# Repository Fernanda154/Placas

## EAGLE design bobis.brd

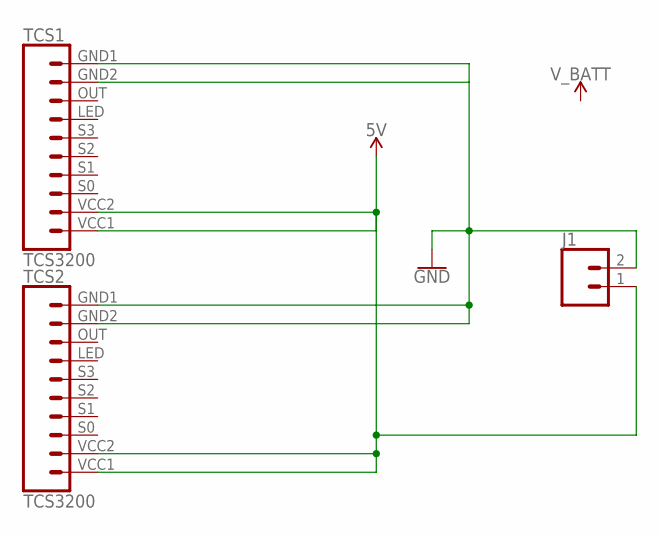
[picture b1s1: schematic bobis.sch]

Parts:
J1: CONN_02; 1X02
TCS1, TCS2: TCS3200

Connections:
5V: J1.1, TCS1.VCC1, TCS1.VCC2, TCS2.VCC1, TCS2.VCC2
GND: J1.2, TCS1.GND1, TCS1.GND2, TCS2.GND1, TCS2.GND2

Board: 2 copper layers, 3 parts (0 on the bottom side), 2 nets, no tracks yet.

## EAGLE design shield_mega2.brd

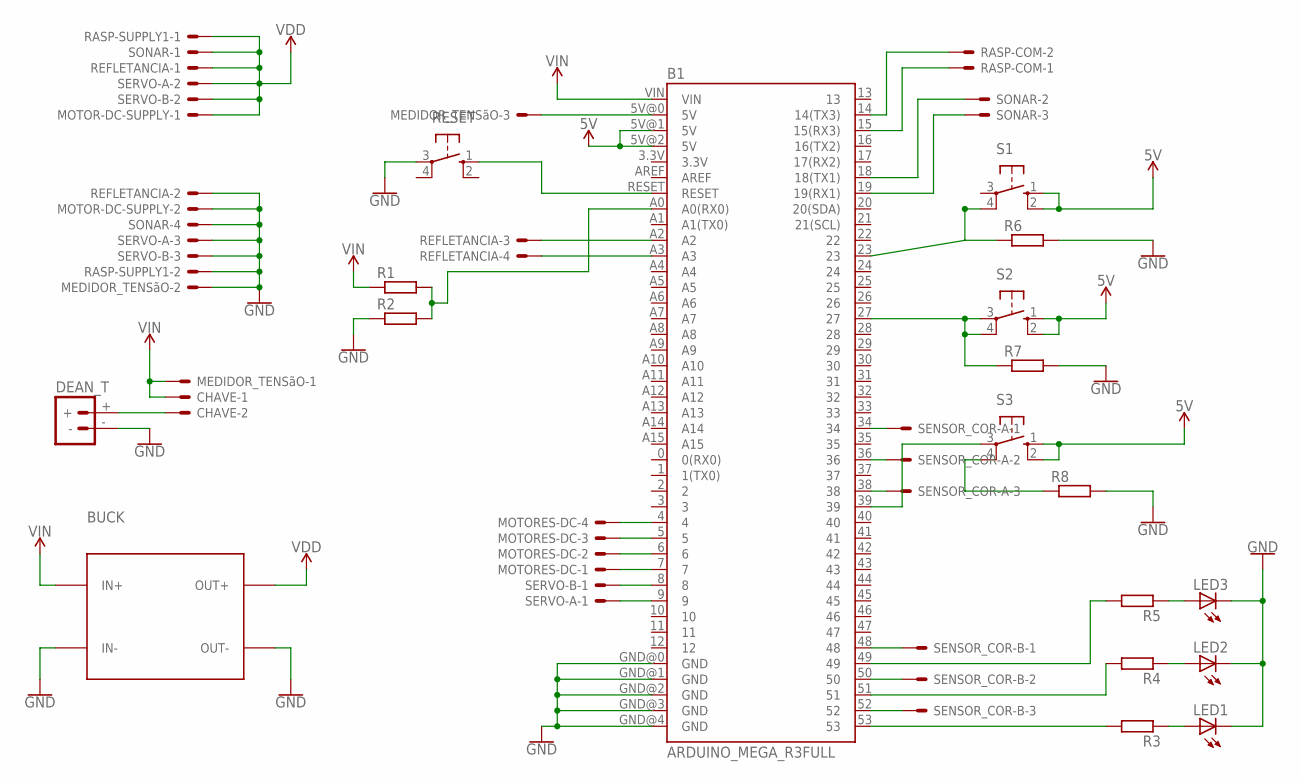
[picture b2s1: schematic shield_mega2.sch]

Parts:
B1: ARDUINO_MEGA_R3FULL; ARDUINO_MEGA
BUCK: DC-DC-STEP-DOWN-LM2596
CHAVE: 22-23-2021
DEAN_T: BATTERY_CONN_DEANS; DEANS
LED1, LED2, LED3: LED5MM
MEDIDOR_TENSãO: 22-23-2031
MOTOR-DC-SUPPLY: 22-23-2021
MOTORES-DC: 22-23-2041
R1, R2: R-EU_0207/12; 0207/12
R3, R4, R5: R-EU_0207/7; 0207/7
R6, R7, R8: R-EU_0204/7; 0204/7
RASP-COM: 22-23-2021
RASP-SUPPLY1: 22-23-2021
REFLETANCIA: 22-23-2041
RESET: 10-XX; B3F-10XX
S1, S2, S3: 10-XX; B3F-10XX
SENSOR_COR-A: 22-23-2031
SENSOR_COR-B: 22-23-2031
SERVO-A: 22-23-2031
SERVO-B: 22-23-2031
SONAR: 22-23-2041

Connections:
5V: B1.5V@1 (5V), B1.5V@2 (5V), S1.1 (S), S1.2 (S1), S2.1 (S), S2.2 (S1), S3.1 (S), S3.2 (S1)
GND: B1.GND@0 (GND), B1.GND@1 (GND), B1.GND@2 (GND), B1.GND@3 (GND), B1.GND@4 (GND), BUCK.IN-, BUCK.OUT-, DEAN_T.-, LED1.K (C), LED2.K (C), LED3.K (C), MEDIDOR_TENSãO.2, MOTOR-DC-SUPPLY.2, R2.1, R6.2, R7.2, R8.2, RASP-SUPPLY1.2, REFLETANCIA.2, RESET.3, SERVO-A.3, SERVO-B.3, SONAR.4
unnamed: B1.A2, REFLETANCIA.3
unnamed: B1.A3, REFLETANCIA.4
unnamed: B1.4, MOTORES-DC.4
unnamed: B1.5, MOTORES-DC.3
unnamed: B1.6, MOTORES-DC.2
unnamed: B1.7, MOTORES-DC.1
unnamed: B1.8, SERVO-B.1
unnamed: B1.9, SERVO-A.1
unnamed: B1.14 (14(TX3)), RASP-COM.2
unnamed: B1.15 (15(RX3)), RASP-COM.1
unnamed: B1.18 (18(TX1)), SONAR.2
unnamed: B1.19 (19(RX1)), SONAR.3
unnamed: CHAVE.2, DEAN_T.+
unnamed: B1.34, SENSOR_COR-A.1
unnamed: B1.36, SENSOR_COR-A.2
unnamed: B1.38, SENSOR_COR-A.3
unnamed: B1.52, SENSOR_COR-B.3
unnamed: B1.50, SENSOR_COR-B.2
unnamed: B1.48, SENSOR_COR-B.1
unnamed: B1.A0 (A0(RX0)), R1.2, R2.2
unnamed: B1.53, R3.2
unnamed: B1.51, R4.2
unnamed: B1.49, R5.2
unnamed: LED3.A, R5.1
unnamed: LED2.A, R4.1
unnamed: LED1.A, R3.1
unnamed: B1.27, R7.1, S2.3, S2.4 (P1)
unnamed: B1.23, R6.1, S1.4 (P1)
unnamed: R8.1, S3.4 (P1)
unnamed: B1.39, S3.3
unnamed: B1.RESET, RESET.1 (S)
unnamed: B1.5V@0 (5V), MEDIDOR_TENSãO.3
VDD: BUCK.OUT+, MOTOR-DC-SUPPLY.1, RASP-SUPPLY1.1, REFLETANCIA.1, SERVO-A.2, SERVO-B.2, SONAR.1
VIN: B1.VIN, BUCK.IN+, CHAVE.1, MEDIDOR_TENSãO.1, R1.1

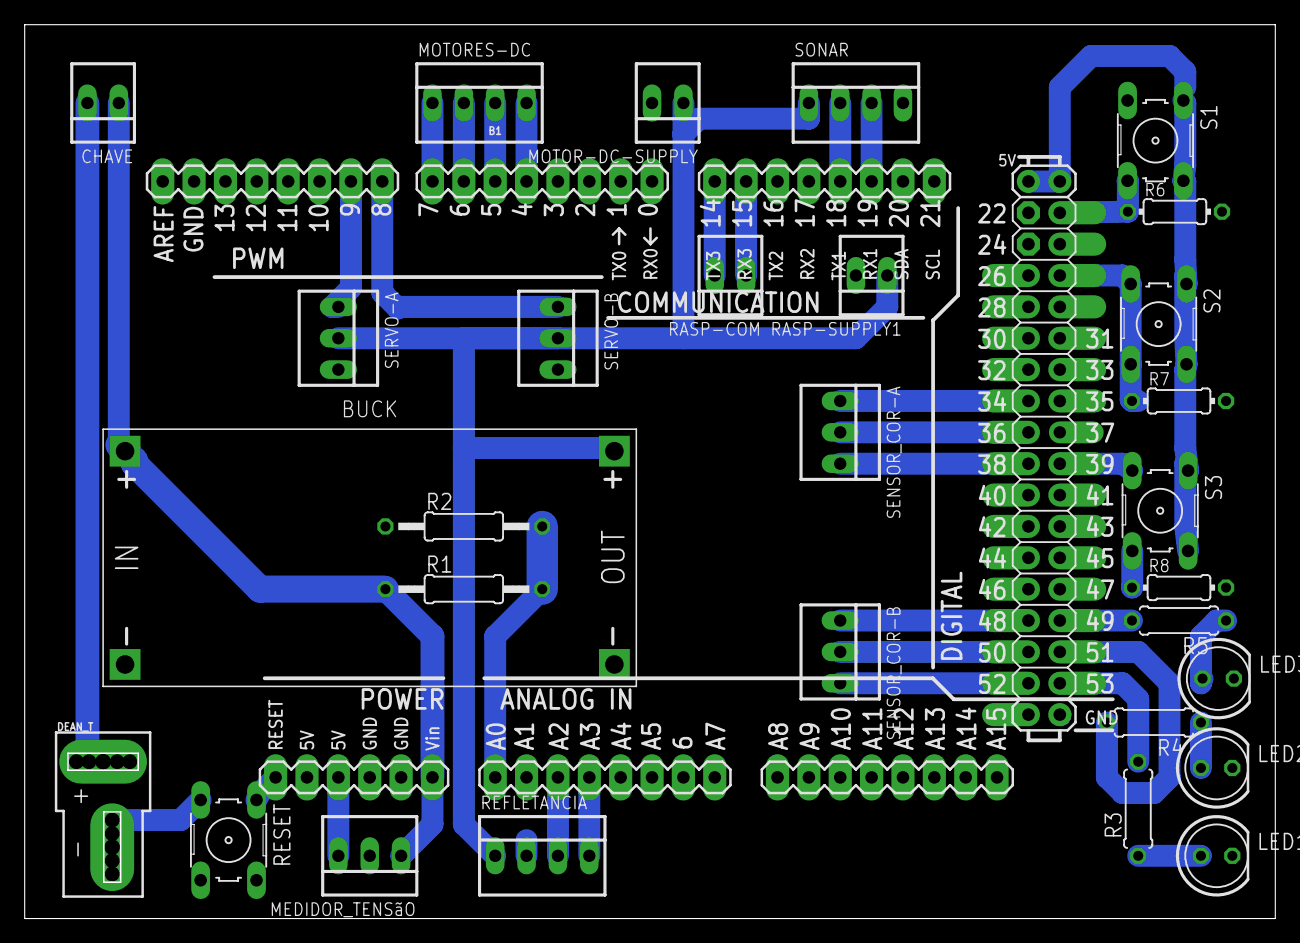
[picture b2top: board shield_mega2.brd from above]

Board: 2 copper layers, 101.1 x 72.3 mm, 30 parts (0 on the bottom side), 36 nets.

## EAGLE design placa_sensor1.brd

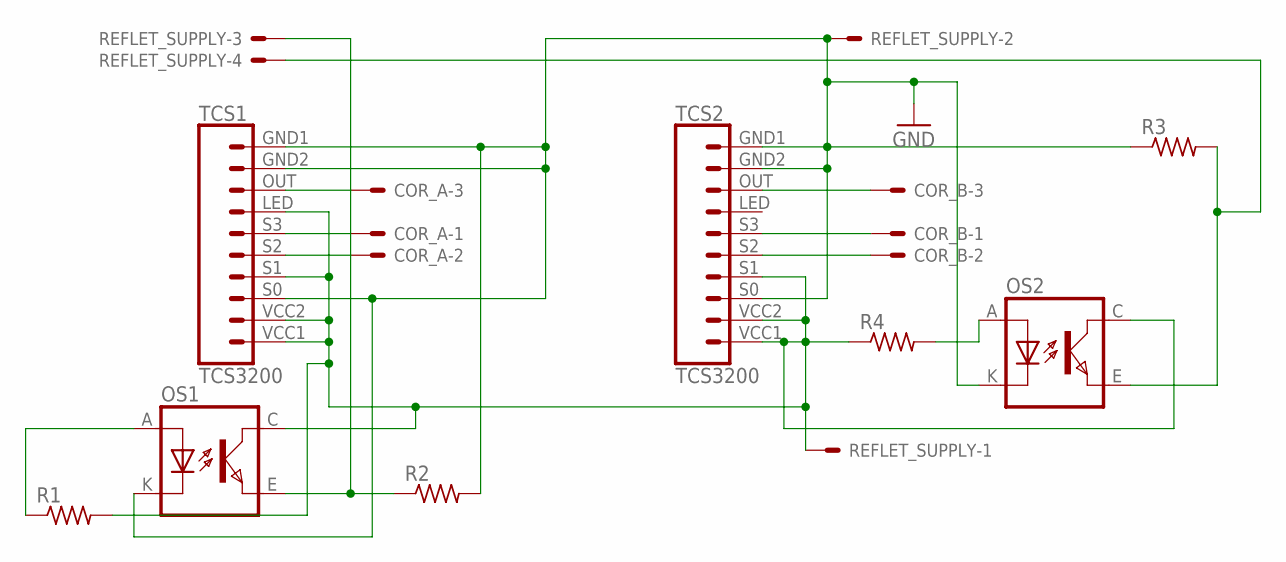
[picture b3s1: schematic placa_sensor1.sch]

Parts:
COR_A: 22-05-7038-03; 7395-03
COR_B: 22-05-7038-03; 7395-03
OS1, OS2: TCRT5000
R1, R2, R3, R4: R-US_0204/5; 0204/5
REFLET_SUPPLY: 22-05-7048-04; 7395-04
TCS1, TCS2: TCS3200

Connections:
GND: OS1.K (CATHODE), OS2.K (CATHODE), R2.2, R3.1, REFLET_SUPPLY.2, TCS1.GND1, TCS1.GND2, TCS1.S0, TCS2.GND1, TCS2.GND2, TCS2.S0
unnamed: COR_A.1, TCS1.S3
unnamed: COR_A.3, TCS1.OUT
unnamed: COR_A.2, TCS1.S2
unnamed: COR_B.2, TCS2.S2
unnamed: COR_B.3, TCS2.OUT
unnamed: COR_B.1, TCS2.S3
unnamed: OS1.A (ANODE), R1.1
unnamed: OS1.E (EMITTER), R2.1, REFLET_SUPPLY.3
unnamed: OS2.E (EMITTER), R3.2, REFLET_SUPPLY.4
unnamed: OS2.A (ANODE), R4.2
unnamed: OS1.C (COLLECTOR), OS2.C (COLLECTOR), R1.2, R4.1, REFLET_SUPPLY.1, TCS1.LED, TCS1.S1, TCS1.VCC1, TCS1.VCC2, TCS2.S1, TCS2.VCC1, TCS2.VCC2

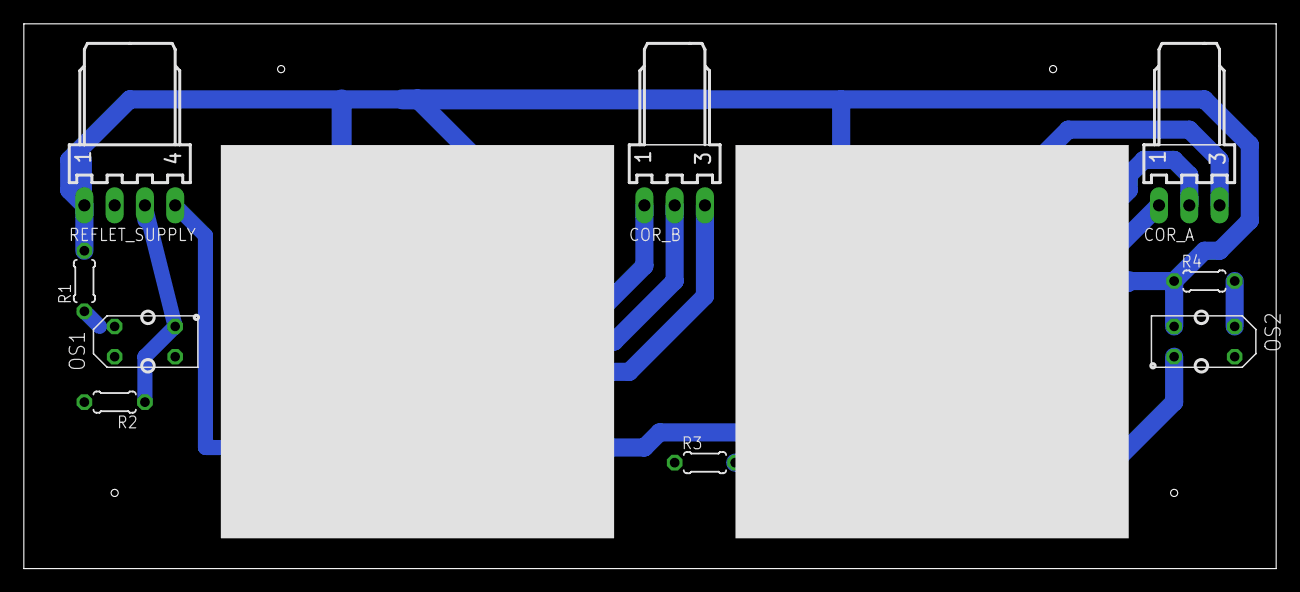
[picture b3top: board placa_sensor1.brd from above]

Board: 2 copper layers, 105.1 x 45.7 mm, 11 parts (0 on the bottom side), 12 nets.

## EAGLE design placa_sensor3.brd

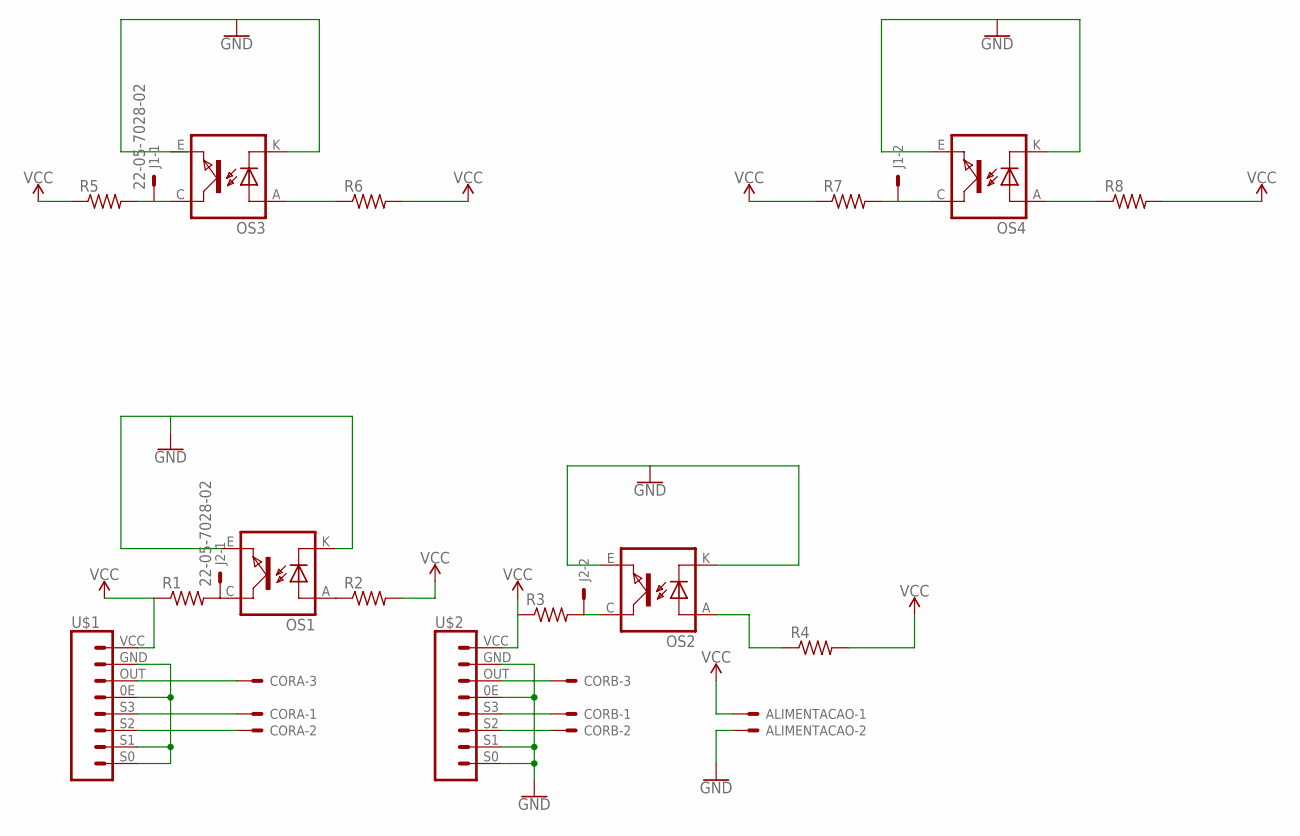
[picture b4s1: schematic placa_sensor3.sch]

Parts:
ALIMENTACAO: 22-05-7028-02; 7395-02
CORA: 22-05-7038-03; 7395-03
CORB: 22-05-7038-03; 7395-03
J1, J2: 22-05-7028-02; 7395-02
OS1, OS2, OS3, OS4: TCRT5000
R1, R2, R3, R4, R5, R6, R7, R8: R-US_0204/5; 0204/5
U$1, U$2: TCS3200_2TCS3200_2; TCS3200_2

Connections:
GND: ALIMENTACAO.2, OS1.E (EMITTER), OS1.K (CATHODE), OS2.E (EMITTER), OS2.K (CATHODE), OS3.K (CATHODE), OS4.E (EMITTER), OS4.K (CATHODE), U$2.0E, U$2.GND, U$2.S0, U$2.S1
unnamed: CORA.2, U$1.S2
unnamed: CORB.1, U$2.S3
unnamed: CORB.2, U$2.S2
unnamed: CORA.3, U$1.OUT
unnamed: CORA.1, U$1.S3
unnamed: CORB.3, U$2.OUT
unnamed: OS1.A (ANODE), R2.1
unnamed: J2.1, OS1.C (COLLECTOR), R1.2
unnamed: J2.2, OS2.C (COLLECTOR), R3.2
unnamed: U$1.0E, U$1.GND, U$1.S0, U$1.S1
unnamed: OS2.A (ANODE), R4.1
unnamed: OS3.A (ANODE), R6.1
unnamed: J1.1, OS3.C (COLLECTOR), R5.2
unnamed: J1.2, OS4.C (COLLECTOR), R7.2
unnamed: OS4.A (ANODE), R8.1
VCC: ALIMENTACAO.1, R1.1, R2.2, R3.1, R4.2, R5.1, R6.2, R7.1, R8.2, U$1.VCC, U$2.VCC

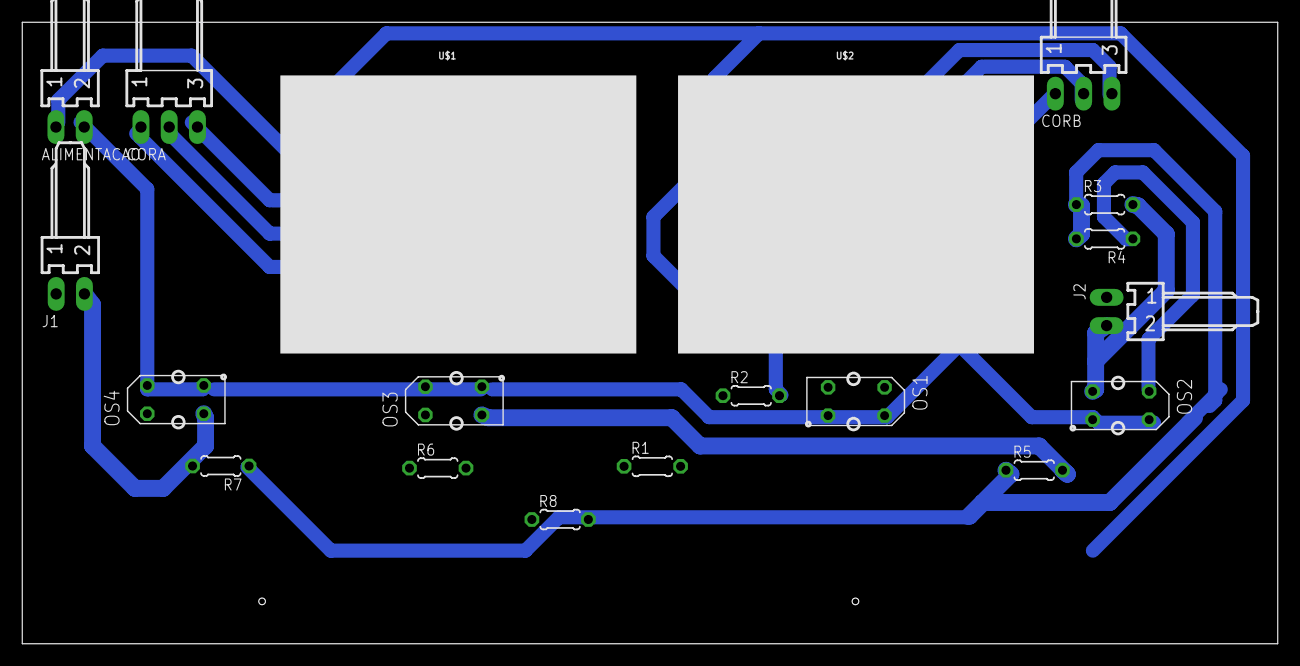
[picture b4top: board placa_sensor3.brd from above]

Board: 2 copper layers, 112.9 x 55.9 mm, 19 parts (0 on the bottom side), 17 nets.

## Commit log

2017-07-26 commit inicial

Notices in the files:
parts and their libraries:
Robotica-IFRN-SC: Licensing: Creative Commons ShareAlike 4.0 International - https://creativecommons.org/licenses/by-sa/4.0
